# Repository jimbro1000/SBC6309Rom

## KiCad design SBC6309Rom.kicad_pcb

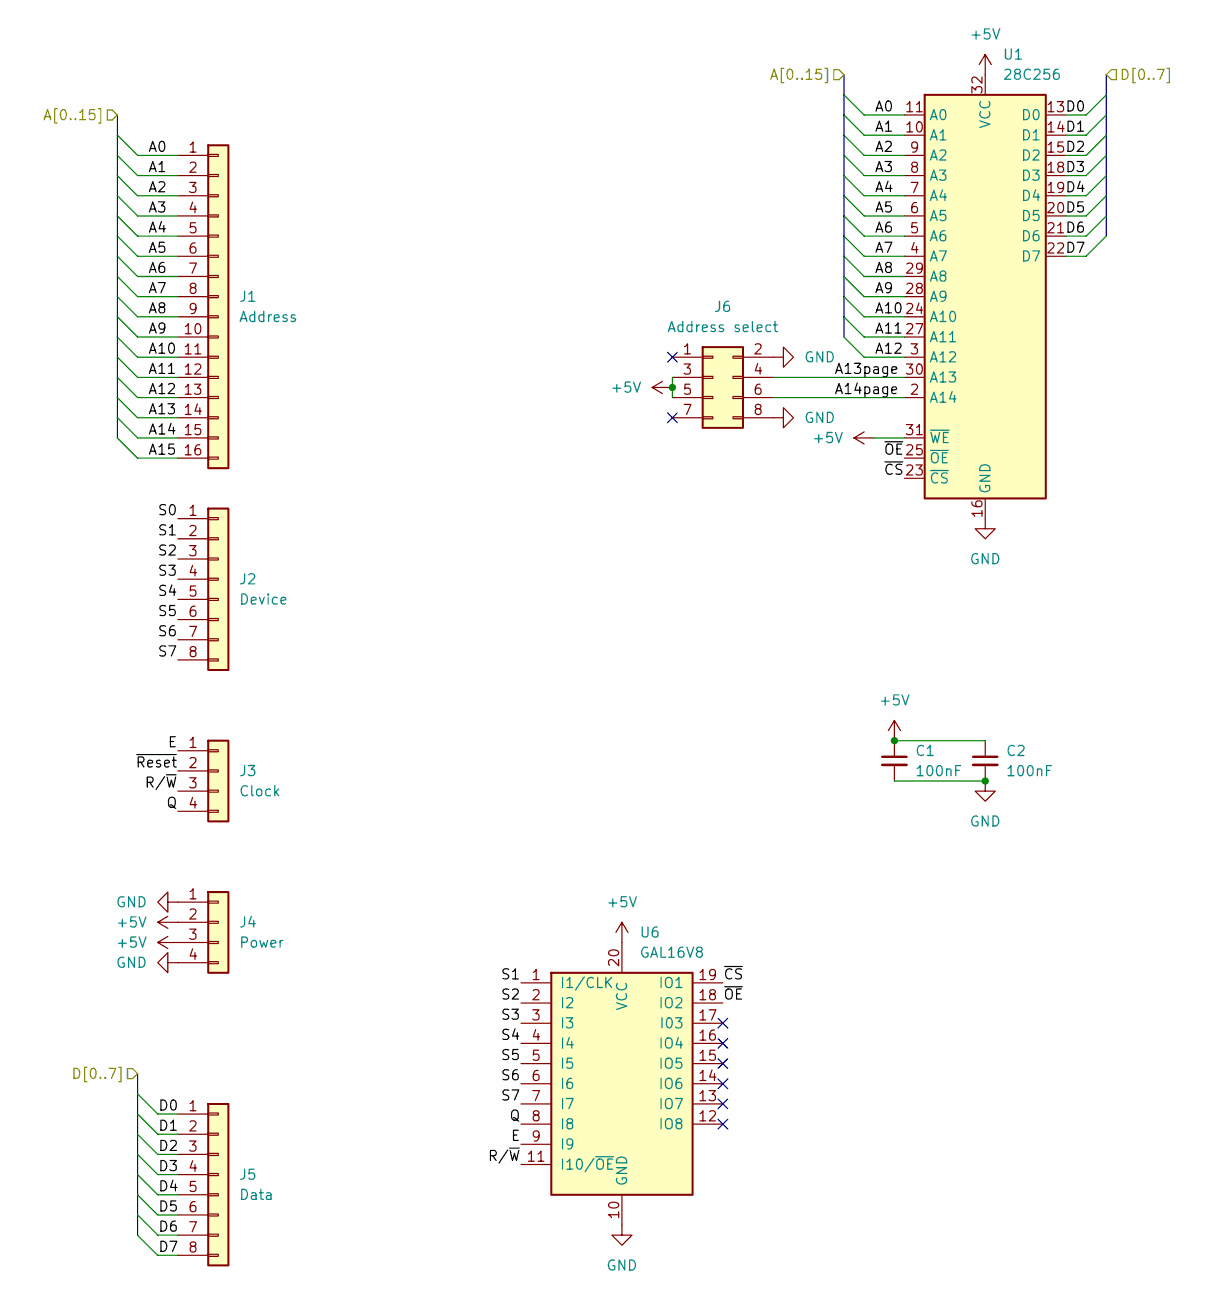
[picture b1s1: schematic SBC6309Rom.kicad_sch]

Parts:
C1, C2: 100nF; C_0805_2012Metric
J1: Address; PinHeader_1x16_P2.54mm_Vertical
J2: Device; PinHeader_1x08_P2.54mm_Vertical
J3: Clock; PinHeader_1x04_P2.54mm_Vertical
J4: Power; PinHeader_1x04_P2.54mm_Vertical
J5: Data; PinHeader_1x08_P2.54mm_Vertical
J6: Address select; PinHeader_2x04_P2.54mm_Vertical
U1: 28C256; PLCC-32_THT-Socket
U6: GAL16V8; PLCC-20_THT-Socket

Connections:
+5V: C1.1, C2.1, J4.2, J4.3, J6.3, J6.5, U1.31 (~WE), U1.32 (VCC), U6.20 (VCC)
/A0: J1.1, U1.11 (A0)
/A1: J1.2, U1.10 (A1)
/A2: J1.3, U1.9 (A2)
/A3: J1.4, U1.8 (A3)
/A4: J1.5, U1.7 (A4)
/A5: J1.6, U1.6 (A5)
/A6: J1.7, U1.5 (A6)
/A7: J1.8, U1.4 (A7)
/A8: J1.9, U1.29 (A8)
/A9: J1.10, U1.28 (A9)
/A10: J1.11, U1.24 (A10)
/A11: J1.12, U1.27 (A11)
/A12: J1.13, U1.3 (A12)
/A13: J1.14
/A13page: J6.4, U1.30 (A13)
/A14: J1.15
/A14page: J6.6, U1.2 (A14)
/A15: J1.16
/D0: J5.1, U1.13 (D0)
/D1: J5.2, U1.14 (D1)
/D2: J5.3, U1.15 (D2)
/D3: J5.4, U1.18 (D3)
/D4: J5.5, U1.19 (D4)
/D5: J5.6, U1.20 (D5)
/D6: J5.7, U1.21 (D6)
/D7: J5.8, U1.22 (D7)
/E: J3.1, U6.9 (I9)
/Q: J3.4, U6.8 (I8)
/R/~W: J3.3, U6.11 (I10/~OE)
/S0: J2.1
/S1: J2.2, U6.1 (I1/CLK)
/S2: J2.3, U6.2 (I2)
/S3: J2.4, U6.3 (I3)
/S4: J2.5, U6.4 (I4)
/S5: J2.6, U6.5 (I5)
/S6: J2.7, U6.6 (I6)
/S7: J2.8, U6.7 (I7)
/~CS: U1.23 (~CS), U6.19 (IO1)
/~OE: U1.25 (~OE), U6.18 (IO2)
/~Reset: J3.2
GND: C1.2, C2.2, J4.1, J4.4, J6.2, J6.8, U1.16 (GND), U6.10 (GND)

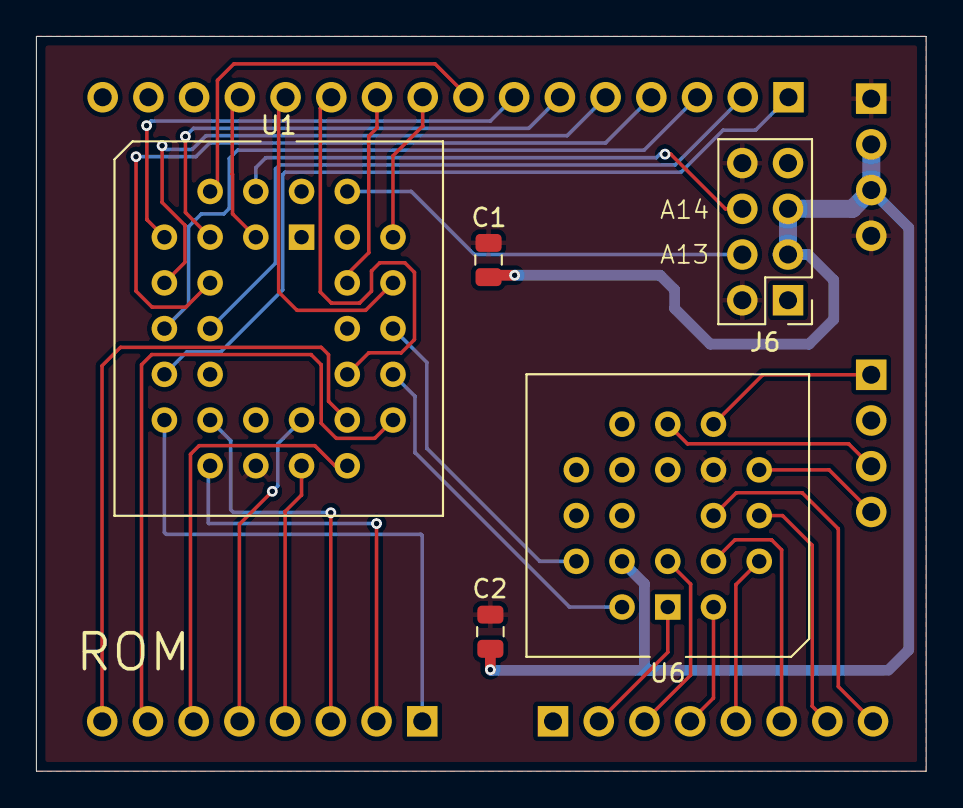
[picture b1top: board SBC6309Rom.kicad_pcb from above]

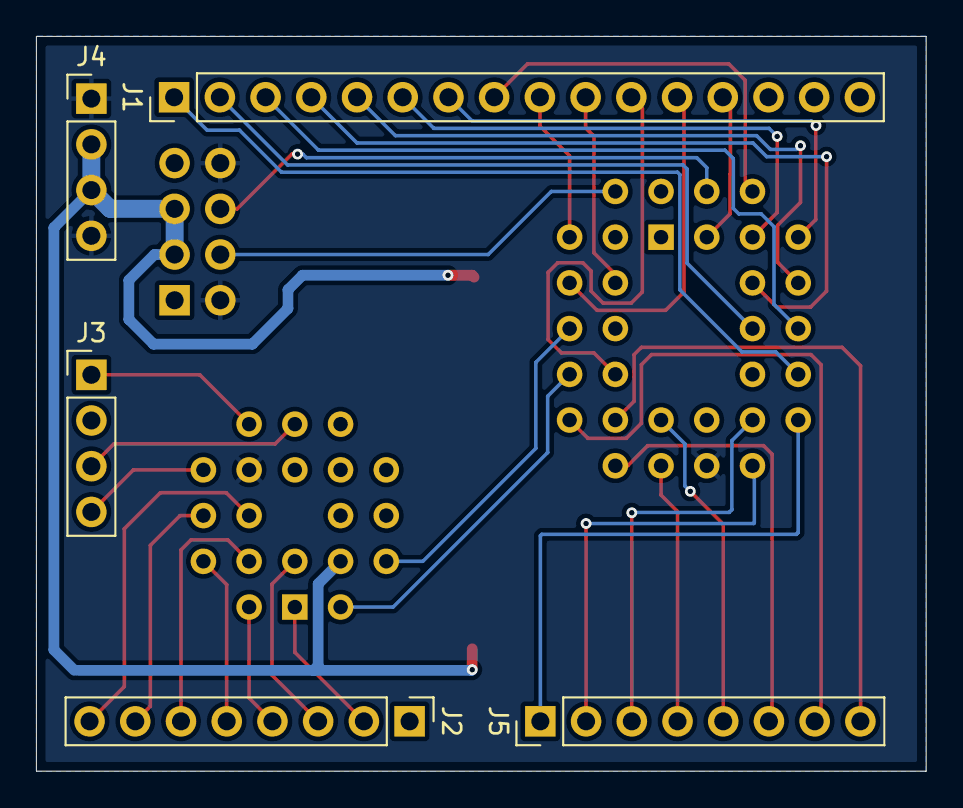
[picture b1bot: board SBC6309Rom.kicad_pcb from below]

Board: 4 copper layers, 49.4 x 40.8 mm, 10 parts (5 on the bottom side), 37 nets.

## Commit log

2025-07-07 fix rom footprint
